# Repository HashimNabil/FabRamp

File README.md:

# FabRamp

Fabramp is Ramp 1.4 fabable board! its based on Atmega2560 and comes with the following features:
- 6 PWM terminals with STP55NF06L transistors that can be used for multiple Extruders/hot bed/fans
- Extruder Fan terminal
- 2 Extruders terminals with built in Polulu drivers (one of them have terminals for external driver)
- 3 Thermometer terminals with filtering capacitors
- Terminals for 3 axis motors (X, Y and Z)
- Terminals for End stops for all Axis (2 per Axis)
- BLtouch Auto level sensor terminals
- ISP headers
- USB support
- 12V Power terminals with 20A diode as reverse voltage protection
- 5V input with 5A diode as reverse voltage protect

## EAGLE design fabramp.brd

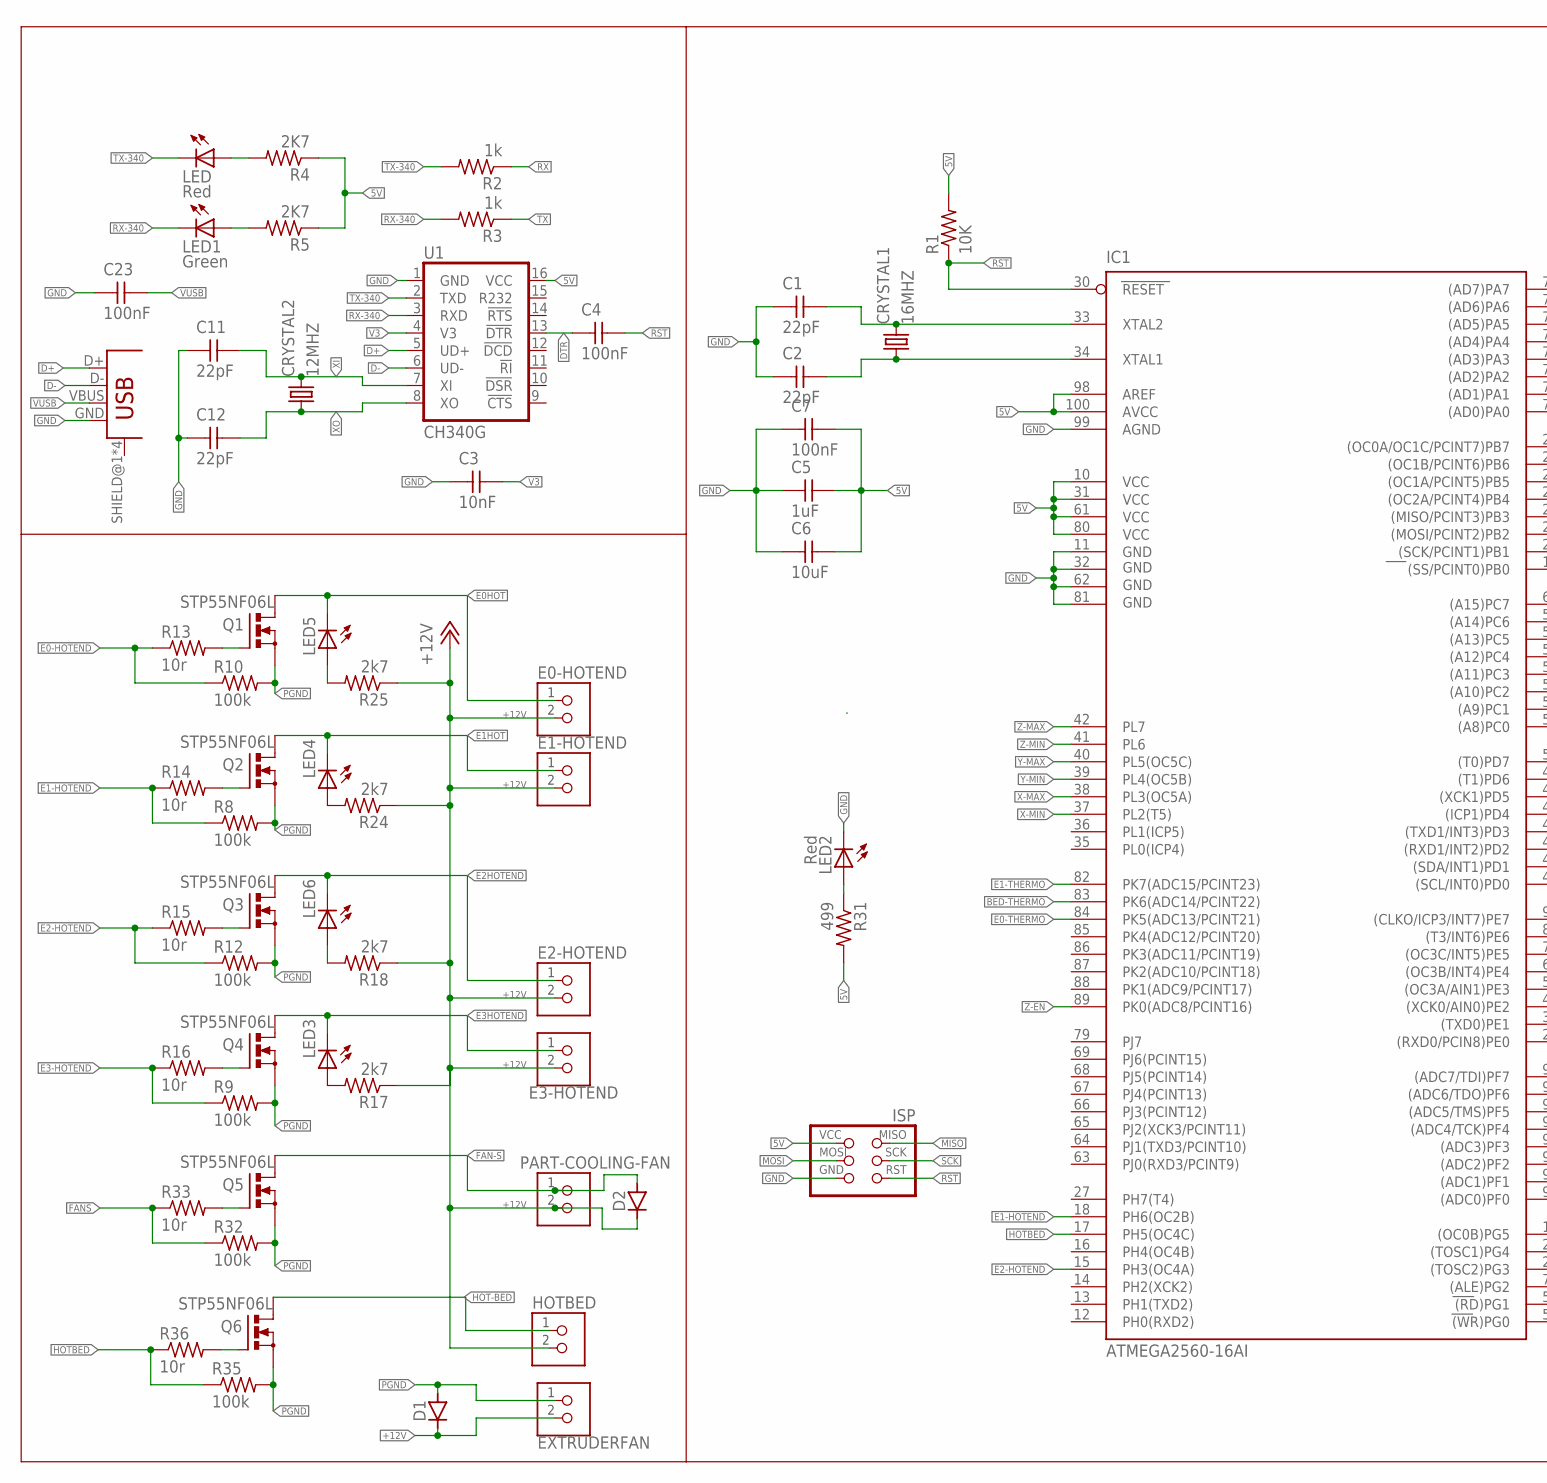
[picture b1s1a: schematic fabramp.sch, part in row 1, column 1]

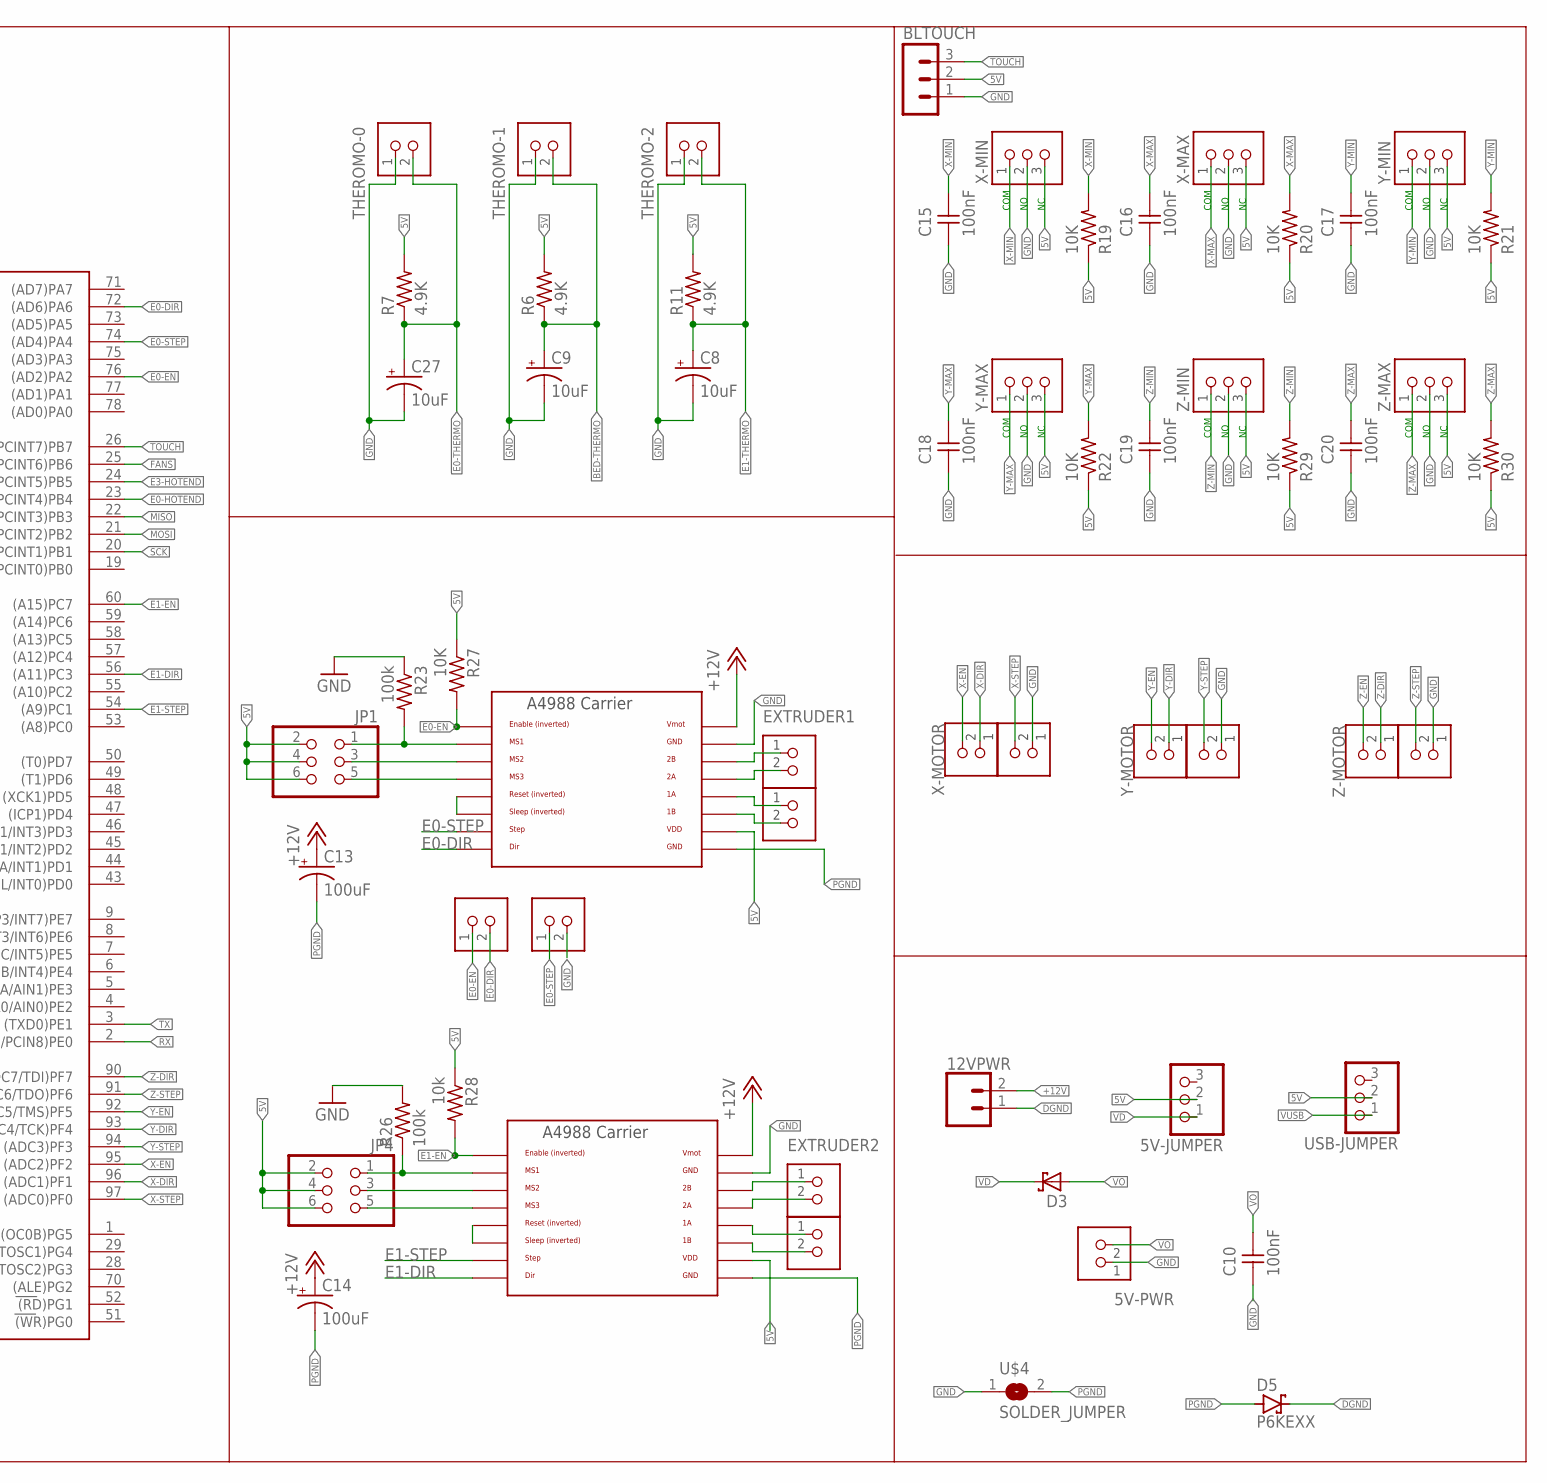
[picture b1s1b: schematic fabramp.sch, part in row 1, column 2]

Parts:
5V-JUMPER: PINHD-1X3; 1X03
5V-PWR: TERM-1X02-FABLAB; ED555DS-2DS
12VPWR: CONN_025MM; SCREWTERMINAL-5MM-2
BLTOUCH: MA03-1
C1, C2, C11, C12: 22pF; C1206FAB
C3: 10nF; C1206FAB
C4, C7, C10, C15, C16, C17, C18, C19, C20, C23: 100nF; C1206FAB
C5: 1uF; C1206FAB
C6: 10uF; C1206FAB
C8, C9, C27: 10uF; 153CLV-0405
C13, C14: 100uF; 153CLV-0605
CRYSTAL1: 16MHZ; CSM-7X-DU
CRYSTAL2: 12MHZ; CSM-7X-DU
D1, D2: CDBM1100-G; MINI-SMA
D3: SCHOTTKY-DIODEDO35-7; DO35-7
D5: P6KEXX; CB417-15
E0-HOTEND, E1-HOTEND, E2-HOTEND, E3-HOTEND: TERM-1X02-FABLAB; ED555DS-2DS
EXTERNAL-EXTRUDER: TERM-1X02-FABLAB; ED555DS-2DS
EXTRUDER1, EXTRUDER2, EXTRUDER11, EXTRUDER22: TERM-1X02-FABLAB; ED555DS-2DS
EXTRUDERFAN: TERM-1X02-FABLAB; ED555DS-2DS
HOTBED: TERM-1X02-FABLAB; ED555DS-2DS
IC1: ATMEGA2560-16AI; TQFP100
ISP: AVRISPSMD; 2X03SMD
JP1, JP4: PINHD-2X3; 2X03
LED, LED2: Red; LED1206FAB
LED1: Green; LED1206FAB
LED3, LED4, LED5, LED6: LEDFAB1206; LED1206FAB
PART-COOLING-FAN: TERM-1X02-FABLAB; ED555DS-2DS
Q1, Q2, Q3, Q4, Q5, Q6: STP55NF06L; TO220BV
R1, R19, R20, R21, R22, R27, R29, R30: 10K; R1206FAB
R2, R3: 1k; R1206FAB
R4, R5: 2K7; R1206FAB
R6, R7, R11: 4.9K; R1206FAB
R8, R9, R10, R12, R23, R26, R32, R35: 100k; R1206FAB
R13, R14, R15, R16, R33, R36: 10r; R1206FAB
R17, R18, R24, R25: 2k7; R1206FAB
R28: 10k; R1206FAB
R31: 499; R1206FAB
THEROMO-0, THEROMO-1, THEROMO-2: TERM-1X02-FABLAB; ED555DS-2DS
U1: CH340G; SO016
U$1: USB_MINIB
U$2, U$3: A4988BREAKOUT
U$4: SOLDER_JUMPER; SJFAB
USB-JUMPER: PINHD-1X3; 1X03
X-MAX: TERM-1X03'-FABLAB'; ED555DS-3DS
X-MIN: TERM-1X03'-FABLAB'; ED555DS-3DS
X-MOTOR, X-MOTOR2: TERM-1X02-FABLAB; ED555DS-2DS
XMOTOR2: TERM-1X02-FABLAB; ED555DS-2DS
Y-MAX: TERM-1X03'-FABLAB'; ED555DS-3DS
Y-MIN: TERM-1X03'-FABLAB'; ED555DS-3DS
Y-MOTOR: TERM-1X02-FABLAB; ED555DS-2DS
YMOTOR2: TERM-1X02-FABLAB; ED555DS-2DS
Z-MAX: TERM-1X03'-FABLAB'; ED555DS-3DS
Z-MIN: TERM-1X03'-FABLAB'; ED555DS-3DS
Z-MOTOR, Z-MOTOR2: TERM-1X02-FABLAB; ED555DS-2DS

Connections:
5V: 5V-JUMPER.2, BLTOUCH.2, C5.2, C6.2, C7.2, IC1.10 (VCC), IC1.31 (VCC1), IC1.61 (VCC2), IC1.80 (VCC3), IC1.98 (AREF), IC1.100 (AVCC), ISP.2 (VCC), JP1.2, JP1.4, JP1.6, JP4.2, JP4.4, JP4.6, R1.2, R4.1, R5.1, R6.2, R7.2, R11.2, R19.1, R20.1, R21.1, R22.1, R27.1, R28.1, R29.1, R30.1, R31.2, U1.16 (VCC), U$2.VDD, U$3.VDD, USB-JUMPER.2, X-MAX.3, X-MIN.3, Y-MAX.3, Y-MIN.3, Z-MAX.3, Z-MIN.3
+12V: 12VPWR.2, C13.+, C14.+, D1.KATHODE, D2.KATHODE, E0-HOTEND.2, E1-HOTEND.2, E2-HOTEND.2, E3-HOTEND.2, EXTRUDERFAN.2, HOTBED.2, PART-COOLING-FAN.2, R17.1, R18.1, R24.1, R25.1, U$2.VMOT, U$3.VMOT
BED-THERMO: C9.+, IC1.83 (PK6(ADC14/PCINT22)), R6.1, THEROMO-1.2
D+: U1.5 (UD+), U$1.D+
D-: U1.6 (UD-), U$1.D-
DGND: 12VPWR.1, D5.C
DTR: C4.1, U1.13 (!DTR)
E0-DIR: EXTERNAL-EXTRUDER.2, IC1.72 ((AD6)PA6), U$2.DIR
E0-EN: EXTERNAL-EXTRUDER.1, IC1.76 ((AD2)PA2), R27.2, U$2.EN
E0-HOTEND: IC1.23 ((OC2A/PCINT4)PB4), R10.1, R13.1
E0-STEP: IC1.74 ((AD4)PA4), U$2.STEP, X-MOTOR2.1
E0-THERMO: C27.+, IC1.84 (PK5(ADC13/PCINT21)), R7.1, THEROMO-0.2
E0HOT: E0-HOTEND.1, LED5.2 (C), Q1.D
E1-DIR: IC1.56 ((A11)PC3), U$3.DIR
E1-EN: IC1.60 ((A15)PC7), R28.2, U$3.EN
E1-HOTEND: IC1.18 (PH6(OC2B)), R8.1, R14.1
E1-STEP: IC1.54 ((A9)PC1), U$3.STEP
E1-THERMO: C8.+, IC1.82 (PK7(ADC15/PCINT23)), R11.1, THEROMO-2.2
E1HOT: E1-HOTEND.1, LED4.2 (C), Q2.D
E2-HOTEND: IC1.15 (PH3(OC4A)), R12.1, R15.1
E2HOTEND: E2-HOTEND.1, LED6.2 (C), Q3.D
E3-HOTEND: IC1.24 ((OC1A/PCINT5)PB5), R9.1, R16.1
E3HOTEND: E3-HOTEND.1, LED3.2 (C), Q4.D
FAN-S: D2.ANODE, PART-COOLING-FAN.1, Q5.D
FANS: IC1.25 ((OC1B/PCINT6)PB6), R32.1, R33.1
GND: 5V-PWR.1, BLTOUCH.1, C1.1, C2.1, C3.1, C5.1, C6.1, C7.1, C8.-, C9.-, C10.1, C11.1, C12.1, C15.1, C16.1, C17.1, C18.1, C19.1, C20.1, C23.1, C27.-, IC1.11 (GND), IC1.32 (GND1), IC1.62 (GND2), IC1.81 (GND3), IC1.99 (AGND), ISP.6 (GND), LED2.2 (C), R23.1, R26.2, THEROMO-0.1, THEROMO-1.1, THEROMO-2.1, U1.1 (GND), U$1.GND, U$2.GND, U$3.GND, U$4.1, X-MAX.2, X-MIN.2, X-MOTOR2.2, XMOTOR2.1, Y-MAX.2, Y-MIN.2, YMOTOR2.1, Z-MAX.2, Z-MIN.2, Z-MOTOR2.1
HOT-BED: HOTBED.1, Q6.D
HOTBED: IC1.17 (PH5(OC4C)), R35.1, R36.1
MISO: IC1.22 ((MISO/PCINT3)PB3), ISP.1 (MISO)
MOSI: IC1.21 ((MOSI/PCINT2)PB2), ISP.4 (MOSI)
unnamed: C1.2, CRYSTAL1.2, IC1.33 (XTAL2)
unnamed: C2.2, CRYSTAL1.1, IC1.34 (XTAL1)
unnamed: LED2.1 (A), R31.1
unnamed: EXTRUDER22.1, U$3.2B
unnamed: EXTRUDER22.2, U$3.2A
unnamed: EXTRUDER2.1, U$3.1A
unnamed: LED.1 (A), R4.2
unnamed: LED1.1 (A), R5.2
unnamed: EXTRUDER2.2, U$3.1B
unnamed: Q5.G, R33.2
unnamed: Q4.G, R16.2
unnamed: Q3.G, R15.2
unnamed: LED3.1 (A), R17.2
unnamed: LED6.1 (A), R18.2
unnamed: Q6.G, R36.2
unnamed: JP1.5, U$2.MS3
unnamed: U$2.RST, U$2.SLP (SLEEP)
unnamed: U$3.RST, U$3.SLP (SLEEP)
unnamed: JP4.1, R26.1, U$3.MS1
unnamed: JP1.1, R23.2, U$2.MS1
unnamed: JP1.3, U$2.MS2
unnamed: JP4.5, U$3.MS3
unnamed: JP4.3, U$3.MS2
unnamed: EXTRUDER11.1, U$2.2B
unnamed: EXTRUDER11.2, U$2.2A
unnamed: EXTRUDER1.1, U$2.1A
unnamed: EXTRUDER1.2, U$2.1B
unnamed: LED4.1 (A), R24.2
unnamed: Q2.G, R14.2
unnamed: Q1.G, R13.2
unnamed: LED5.1 (A), R25.2
PGND: C13.-, C14.-, D1.ANODE, D5.A, EXTRUDERFAN.1, Q1.S, Q2.S, Q3.S, Q4.S, Q5.S, Q6.S, R8.2, R9.2, R10.2, R12.2, R32.2, R35.2, U$2.GND@0 (GND), U$3.GND@0 (GND), U$4.2
RST: C4.2, IC1.30 (RESET), ISP.5 (RST), R1.1
RX: IC1.2 ((RXD0/PCIN8)PE0), R2.1
RX-340: LED1.2 (C), R3.2, U1.3 (RXD)
SCK: IC1.20 ((SCK/PCINT1)PB1), ISP.3 (SCK)
TOUCH: BLTOUCH.3, IC1.26 ((OC0A/OC1C/PCINT7)PB7)
TX: IC1.3 ((TXD0)PE1), R3.1
TX-340: LED.2 (C), R2.2, U1.2 (TXD)
V3: C3.2, U1.4 (V3)
VD: 5V-JUMPER.1, D3.C
VO: 5V-PWR.2, C10.2, D3.A
VUSB: C23.2, U$1.VBUS, USB-JUMPER.1
X-DIR: IC1.96 ((ADC1)PF1), X-MOTOR.1
X-EN: IC1.95 ((ADC2)PF2), X-MOTOR.2
X-MAX: C16.2, IC1.38 (PL3(OC5A)), R20.2, X-MAX.1
X-MIN: C15.2, IC1.37 (PL2(T5)), R19.2, X-MIN.1
X-STEP: IC1.97 ((ADC0)PF0), XMOTOR2.2
XI: C11.2, CRYSTAL2.2, U1.7 (XI)
XO: C12.2, CRYSTAL2.1, U1.8 (XO)
Y-DIR: IC1.93 ((ADC4/TCK)PF4), Y-MOTOR.1
Y-EN: IC1.92 ((ADC5/TMS)PF5), Y-MOTOR.2
Y-MAX: C18.2, IC1.40 (PL5(OC5C)), R22.2, Y-MAX.1
Y-MIN: C17.2, IC1.39 (PL4(OC5B)), R21.2, Y-MIN.1
Y-STEP: IC1.94 ((ADC3)PF3), YMOTOR2.2
Z-DIR: IC1.90 ((ADC7/TDI)PF7), Z-MOTOR.1
Z-EN: IC1.89 (PK0(ADC8/PCINT16)), Z-MOTOR.2
Z-MAX: C20.2, IC1.42 (PL7), R30.2, Z-MAX.1
Z-MIN: C19.2, IC1.41 (PL6), R29.2, Z-MIN.1
Z-STEP: IC1.91 ((ADC6/TDO)PF6), Z-MOTOR2.2

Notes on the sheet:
COM

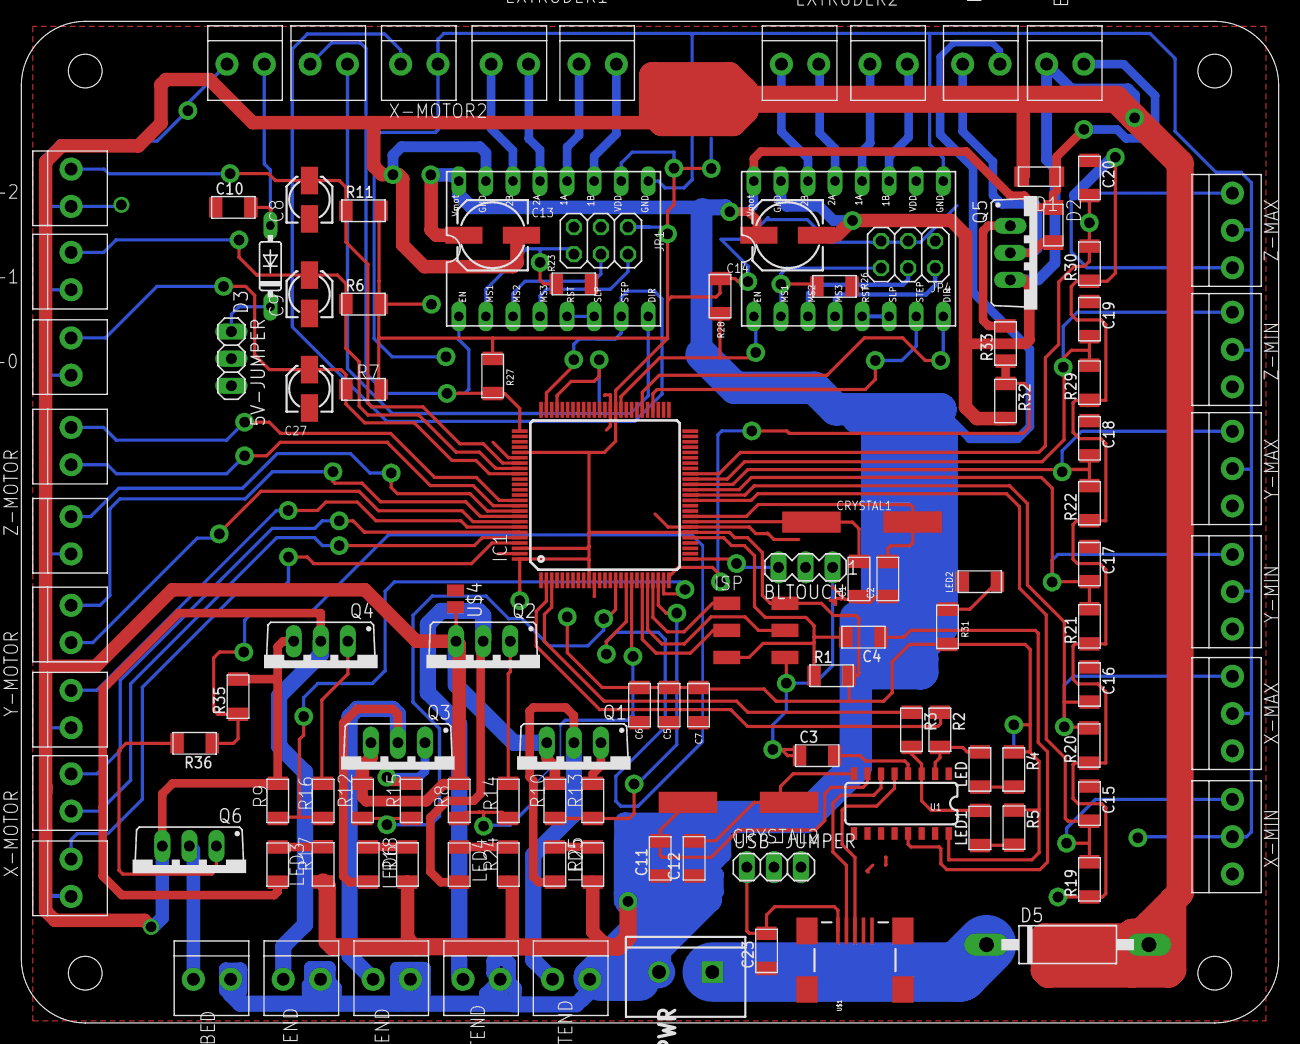
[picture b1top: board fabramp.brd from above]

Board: 2 copper layers, 118.0 x 94.0 mm, 118 parts (0 on the bottom side), 90 nets.

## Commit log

2020-04-18 first commoit
2020-04-18 added documentation
2020-04-18 fixed the image
2021-01-11 added holes

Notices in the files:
parts and their libraries:
SparkFun-Retired: Licensing: Creative Commons ShareAlike 4.0 International - https://creativecommons.org/licenses/by-sa/4.0
